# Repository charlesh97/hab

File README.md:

# HAB — High Altitude Balloon Project

## Overview

This project builds a high‑altitude balloon payload and matching ground station capable of:
- Capturing and transmitting onboard sensor data and imagery from the stratosphere
- Streaming a high‑bandwidth video downlink using DVB‑S2
- Sending a robust QPSK packet telemetry link for flight state (GPS, altitude, environment)

## Quick Start

Want to run the composite link yourself? See **[docs/RF_LINK_RUNBOOK.md](docs/RF_LINK_RUNBOOK.md)** —
hardware, validated config, full TX/RX parameter breakdown, video bridge,
soak harness, and known gotchas.

## System Architecture

### Balloon Payload
- Embedded Linux board (Rock 2A / Orange Pi Zero 3)
- HackRF SDR as RF front end for transmission
- Cameras for video capture
- Weather and atmospheric sensors (see Sensor Suite)

### RF Links (two downlinks)
1. Video downlink: DVB‑S2
2. Telemetry downlink: QPSK packet telemetry (GPS, barometric altitude, temperature, etc.)

### Ground Station
- HackRF SDR receiver
- Custom GUI in `gui/` to:
  - Demodulate DVB‑S2 video
  - Demodulate QPSK telemetry packets
  - Provide real‑time spectrum analysis and monitoring
  - Display and log telemetry

## Repository Structure (empty, still building out)
```
hab/
├── gui/          # Ground station GUI (PySide6 + GNU Radio + SoapySDR)
├── firmware/        # ESP32 + Zephyr RTOS firmware (sensors/control as needed)
├── rf/          # RF link utilities, GNU Radio graphs, tools
├── mechanical/       # Mechanical designs and enclosure files
├── photos/           # Project photos and documentation images
└── README.md         # This file
```

Refer to `gui/README.md` for detailed ground‑station setup (GNU Radio, SoapySDR, HackRF) and run instructions.

## Current Status
- ✅ Ground station GUI scaffolding complete; HackRF integration in place
- 🚧 Bringing up GUI ground station to receive DVB‑S2 video and QPSK telemetry
- 📋 Next: Full telemetry pipeline and end‑to‑end flight test

## Sensor Suite (examples)

### Core sensors (essential)
- BME280/BME680 — Temperature, pressure, humidity (I2C)
- GPS module (u‑blox NEO‑M8N/M9N class) — Lat/Lon/Altitude, velocity (UART)

### Extended sensors (recommended)
- VEML6075 — UVA/UVB index (I2C)
- MQ131 (or electrochemical O3 sensor) — Ozone concentration (analog)
- PMS5003 — Particulate matter PM2.5/PM10 (UART)
- Geiger counter module — Cosmic radiation (pulse count)
- MAG3110 (or HMC5883L) — Magnetometer (I2C)
- MPU6050 (or ICM‑20948) — IMU 6‑9 DOF (I2C/SPI)

## Getting Started (Ground Station)
1. See `gui/README.md` for system dependencies (Homebrew installs), venv setup, and running the app
2. Connect HackRF, configure frequency/sample rate/gains in the Connection tab
3. Start reception in the Telemetry tab; verify spectrum and packet flow

## References
- Orange Pi Zero 3 documentation (see PDFs in repo root)
- GNU Radio project and DVB‑S2 resources
- HackRF documentation (Great Scott Gadgets)

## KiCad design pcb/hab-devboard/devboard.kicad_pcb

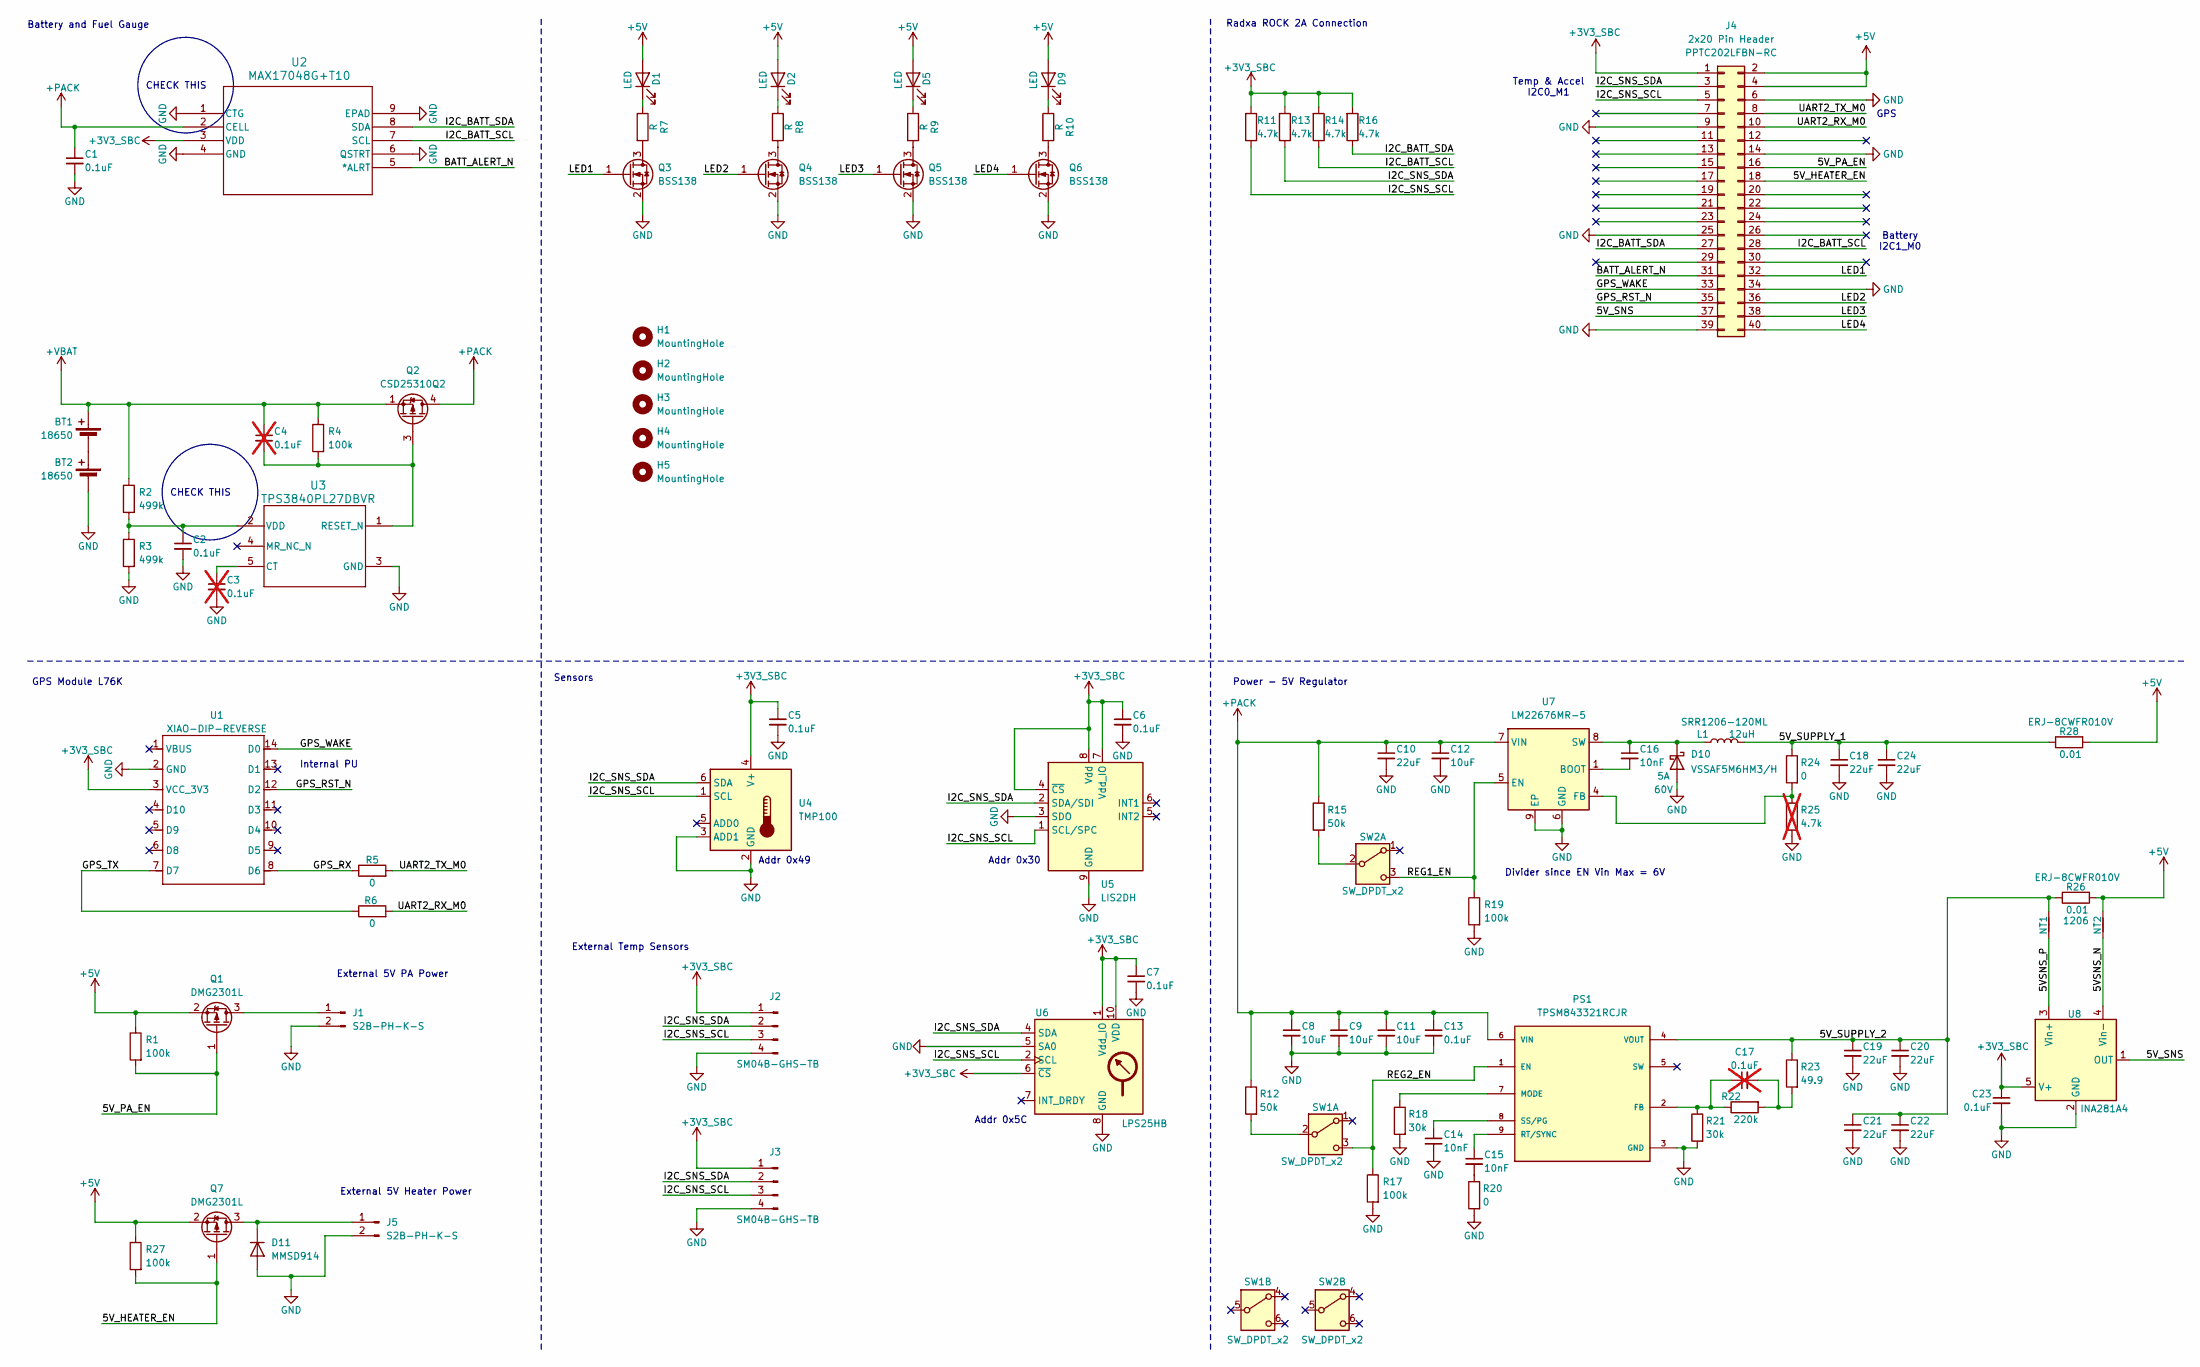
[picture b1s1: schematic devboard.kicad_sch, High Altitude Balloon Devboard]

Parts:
BT1, BT2: 18650; KEYSTONE_54_18650
C1, C2, C5, C6, C7, C13, C23: 0.1uF; C_0402_1005Metric
C3, C4, C17: 0.1uF; C_0402_1005Metric; not fitted
C8, C9, C11, C12: 10uF; C_0805_2012Metric
C10, C18, C19, C20, C21, C22, C24: 22uF; C_1206_3216Metric
C14, C15, C16: 10nF; C_0402_1005Metric
D1, D2, D5, D9: LED; LED_0805_2012Metric
D10: VSSAF5M6HM3/H; VISHAY_DO_221AC; Voltage 60V
D11: MMSD914; D_SOD-123
H1, H2, H3, H4, H5: MountingHole; MountingHole_3.2mm_M3
J1, J5: S2B-PH-K-S; JST_PH_S2B-PH-K_1x02_P2.00mm_Horizontal
J2, J3: SM04B-GHS-TB; JST_GH_SM04B-GHS-TB_1x04-1MP_P1.25mm_Horizontal
J4: 2x20 Pin Header; PinSocket_2x20_P2.54mm_Vertical; Part Number PPTC202LFBN-RC
L1: 12uH; IND_BOURNS_SRR1206; Part Number SRR1206-120ML
NT1, NT2: NetTie_2; NetTie-2_SMD_Pad0.5mm
PS1: TPSM843321RCJR; MODULE_TPSM843321RCJR; PARTREV March 2025
Q1, Q7: DMG2301L; SOT-23
Q2: CSD25310Q2; Texas_DQK
Q3, Q4, Q5, Q6: BSS138; SOT-23
R1, R4, R17, R19, R27: 100k; R_0603_1608Metric
R2, R3: 499k; R_0603_1608Metric
R5, R6, R20, R24: 0; R_0603_1608Metric
R7, R8, R9, R10: R; R_0603_1608Metric
R11, R13, R14, R16: 4.7k; R_0603_1608Metric
R12, R15: 50k; R_0603_1608Metric
R18, R21: 30k; R_0603_1608Metric
R22: 220k; R_0603_1608Metric
R23: 49.9; R_0603_1608Metric
R25: 4.7k; R_0603_1608Metric; not fitted
R26, R28: 0.01; R_1206_3216Metric; Part Number ERJ-8CWFR010V
SW1, SW2: SW_DPDT_x2; SW_DPDT_CK_JS202011JCQN
U1: XIAO-DIP-REVERSE; XIAO-DIP-SMT
U2: MAX17048G+T10; MAX17048_DFN
U3: TPS3840PL27DBVR; SOT-23-5
U4: TMP100; SOT-23-6
U5: LIS2DH; LGA-14_2x2mm_P0.35mm_LayoutBorder3x4y
U6: LPS25HB; ST_HLGA-10_2.5x2.5mm_P0.6mm_LayoutBorder3x2y
U7: LM22676MR-5; TI_SO-PowerPAD-8
U8: INA281A4; SOT-23-5

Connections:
+3V3_SBC: C5.1, C6.1, C7.1, C23.1, J2.1, J3.1, J4.1, R11.2, R13.2, R14.2, R16.2, U1.3 (VCC_3V3), U2.3 (VDD), U4.4 (V+), U5.4 (~CS), U5.7 (Vdd_IO), U5.8 (Vdd), U6.1 (Vdd_IO), U6.6 (~CS), U6.10 (VDD), U8.5 (V+)
+5V: D1.2 (A), D2.2 (A), D5.2 (A), D9.2 (A), J4.2, J4.4, NT2.2, Q1.2 (S), Q7.2 (S), R1.1, R26.2, R27.1, R28.2
+PACK: C1.1, C8.1, C9.1, C10.1, C11.1, C12.1, C13.1, PS1.6 (VIN), Q2.4 (D), Q2.7 (D), R12.1, R15.1, U2.2 (CELL), U7.7 (VIN)
+VBAT: BT1.1 (+), C4.1, Q2.1 (S), Q2.2 (S), Q2.5 (S), Q2.6 (S), Q2.8 (S), R2.1, R4.1
/5VSNS_N: NT2.1, U8.4 (Vin-)
/5VSNS_P: NT1.1, U8.3 (Vin+)
/5V_HEATER_EN: J4.18, Q7.1 (G), R27.2
/5V_PA_EN: J4.16, Q1.1 (G), R1.2
/5V_SNS: J4.37, U8.1 (OUT)
/5V_SUPPLY_1: C18.1, C24.1, L1.2, R24.1, R28.1
/5V_SUPPLY_2: C19.1, C20.1, C21.1, C22.1, NT1.2, PS1.4 (VOUT), R23.1, R26.1
/BATT_ALERT_N: J4.31, U2.5 (*ALRT)
/GPS_RST_N: J4.35, U1.12 (D2)
/GPS_RX: R5.1, U1.8 (D6)
/GPS_TX: R6.1, U1.7 (D7)
/GPS_WAKE: J4.33, U1.14 (D0)
/I2C_BATT_SCL: J4.28, R14.1, U2.7 (SCL)
/I2C_BATT_SDA: J4.27, R16.1, U2.8 (SDA)
/I2C_SNS_SCL: J2.3, J3.3, J4.5, R11.1, U4.1 (SCL), U5.1 (SCL/SPC), U6.2 (SCL)
/I2C_SNS_SDA: J2.2, J3.2, J4.3, R13.1, U4.6 (SDA), U5.2 (SDA/SDI), U6.4 (SDA)
/LED1: J4.32, Q3.1 (G)
/LED2: J4.36, Q4.1 (G)
/LED3: J4.38, Q5.1 (G)
/LED4: J4.40, Q6.1 (G)
/REG1_EN: R19.1, SW2.3 (C), U7.5 (EN)
/REG2_EN: PS1.1 (EN), R17.1, SW1.3 (C)
/UART2_RX_M0: J4.10, R6.2
/UART2_TX_M0: J4.8, R5.2
GND: BT2.2 (-), C1.2, C2.2, C3.2, C5.2, C6.2, C7.2, C8.2, C9.2, C10.2, C11.2, C12.2, C13.2, C14.2, C18.2, C19.2, C20.2, C21.2, C22.2, C23.2, C24.2, D10.2 (A), D11.2 (A), J1.2, J2.4, J3.4, J4.6, J4.9, J4.14, J4.25, J4.34, J4.39, J5.2, PS1.3 (GND), Q3.2 (S), Q4.2 (S), Q5.2 (S), Q6.2 (S), R3.2, R17.2, R18.2, R19.2, R20.2, R21.2, R25.2, U1.2 (GND), U2.1 (CTG), U2.4 (GND), U2.6 (QSTRT), U2.9 (EPAD), U3.3 (GND), U4.2 (GND), U4.3 (ADD1), U5.3 (SDO), U5.9 (GND), U5.10 (GND), U5.11 (GND), U5.12 (GND), U5.13 (GND), U5.14 (GND), U6.3 (GND), U6.5 (SA0), U6.8 (GND), U6.9 (GND), U7.6 (GND), U7.9 (EP), U8.2 (GND)
unnamed: BT1.2 (-), BT2.1 (+)
unnamed: C15.2, R20.1
unnamed: C17.2, R22.2, R23.2
unnamed: D1.1 (K), R7.1
unnamed: D2.1 (K), R8.1
unnamed: D5.1 (K), R9.1
unnamed: D9.1 (K), R10.1
unnamed: C16.1, D10.1 (K), L1.1, U7.8 (SW)
unnamed: D11.1 (K), J5.1, Q7.3 (D)
unnamed: J1.1, Q1.3 (D)
unnamed: C17.1, PS1.2 (FB), R21.1, R22.1
unnamed: PS1.7 (MODE), R18.1
unnamed: C15.1, PS1.9 (RT/SYNC)
unnamed: C14.1, PS1.8 (SS/PG)
unnamed: C4.2, Q2.3 (G), R4.2, U3.1 (RESET_N)
unnamed: Q3.3 (D), R7.2
unnamed: Q4.3 (D), R8.2
unnamed: Q5.3 (D), R9.2
unnamed: Q6.3 (D), R10.2
unnamed: R12.2, SW1.2 (B)
unnamed: R15.2, SW2.2 (B)
unnamed: C3.1, U3.5 (CT)
unnamed: C2.1, R2.2, R3.1, U3.2 (VDD)
unnamed: C16.2, U7.1 (BOOT)
unnamed: R24.2, R25.1, U7.4 (FB)

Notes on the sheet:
Temp & Accel I2C0_M1
Addr 0x49
Power - 5V Regulator
CHECK THIS
External 5V Heater Power
GPS
Battery and Fuel Gauge
Addr 0x5C
Addr 0x30
External 5V PA Power
External Temp Sensors
GPS Module L76K
Radxa ROCK 2A Connection
Battery I2C1_M0
Sensors
Divider since EN Vin Max = 6V
Internal PU

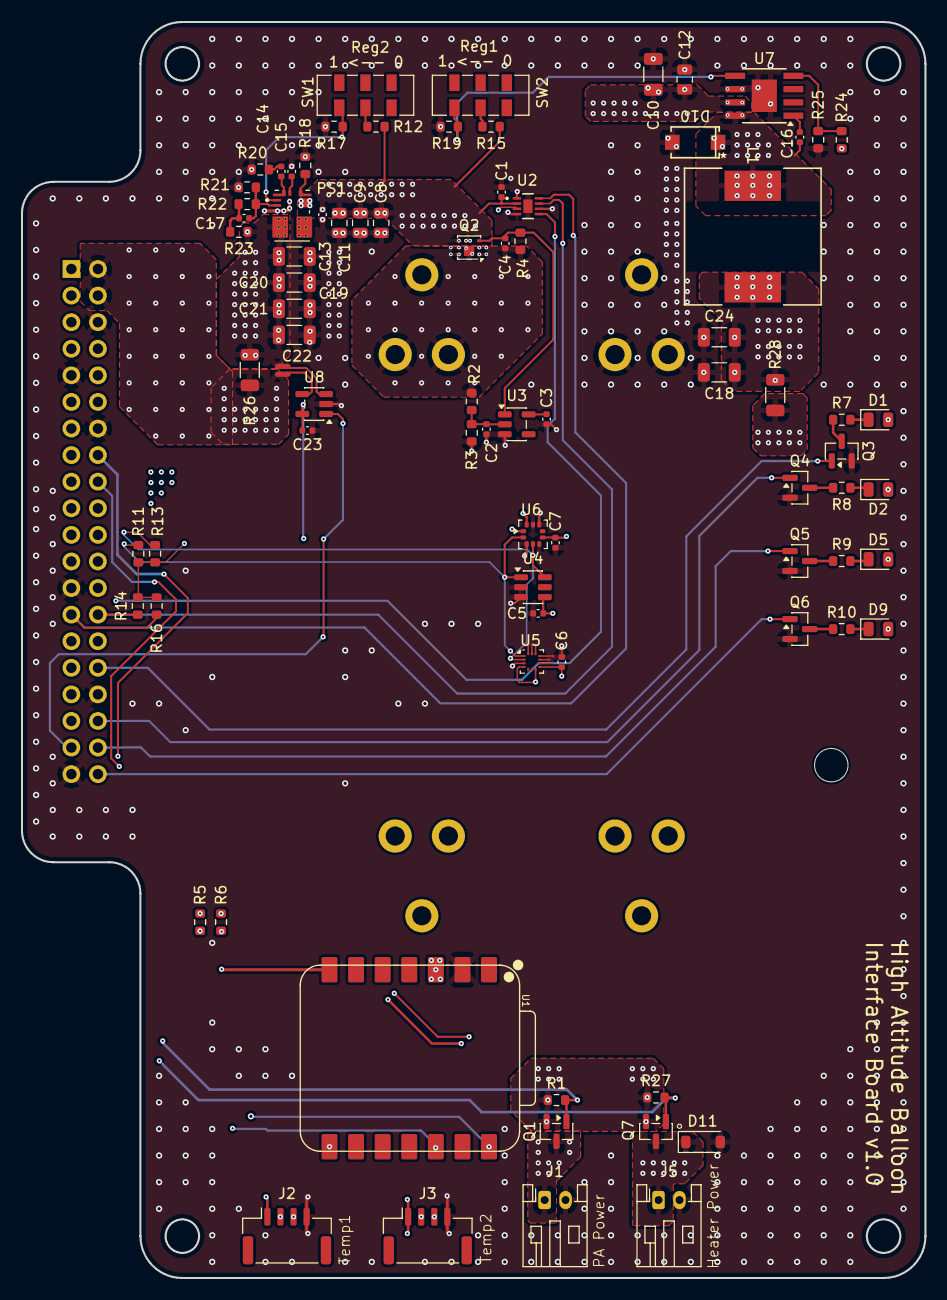
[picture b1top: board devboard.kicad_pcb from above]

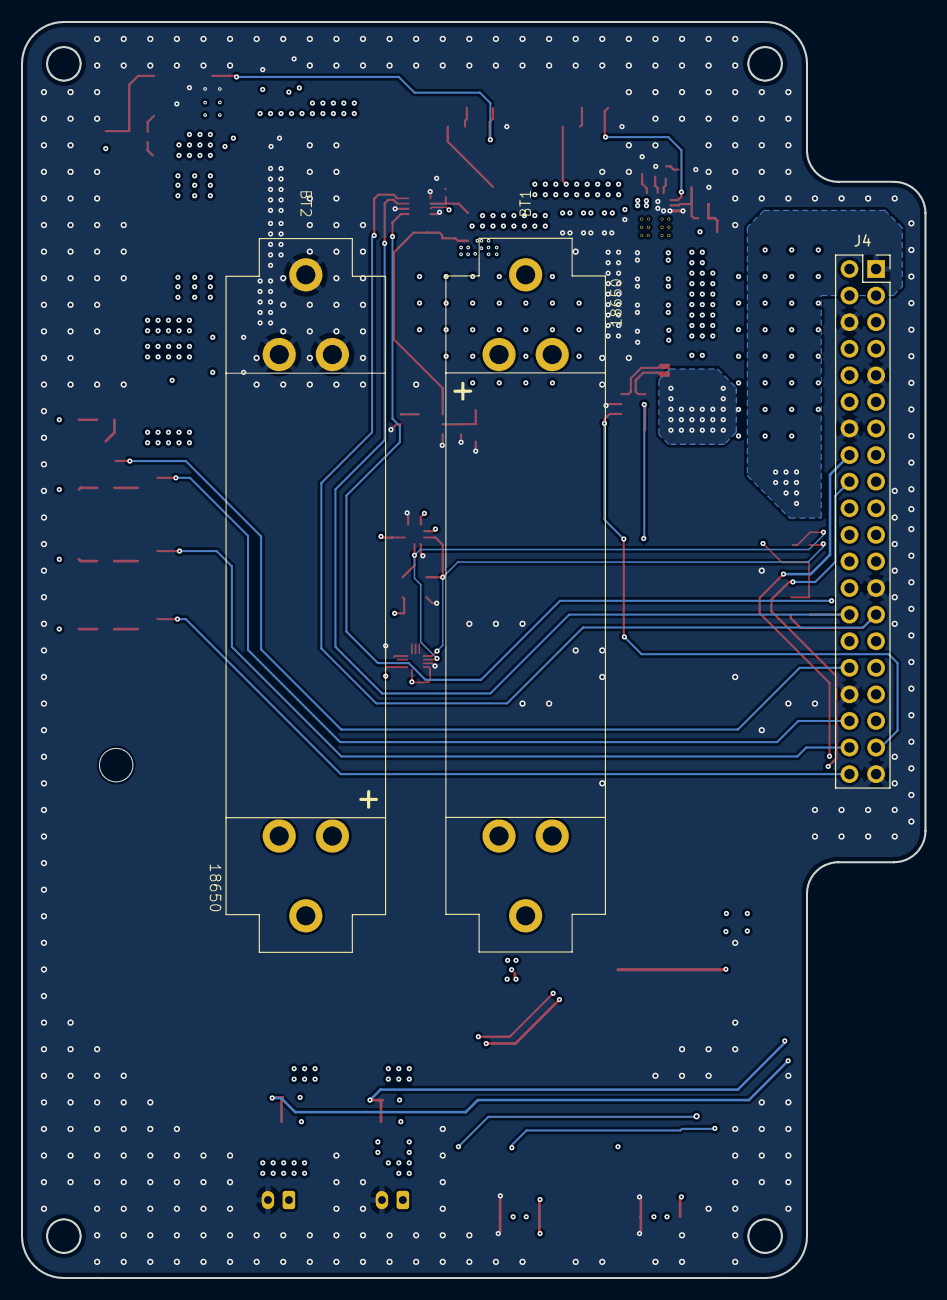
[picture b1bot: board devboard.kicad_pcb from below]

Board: 4 copper layers, 86.3 x 120.0 mm, 91 parts (3 on the bottom side), 54 nets.

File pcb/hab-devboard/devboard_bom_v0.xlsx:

devboard
Reference | Qty | Value | DNP | Exclude from BOM | Exclude from Board | Footprint | Datasheet | Part Number
BT1,BT2 | 2 | 18650 |  |  |  | hab_library:KEYSTONE_54_18650 | ~
C1,C2,C5,C6,C7,C13,C23 | 7 | 0.1uF |  |  |  | Capacitor_SMD:C_0402_1005Metric | ~
C3,C4,C17 | 3 | 0.1uF | DNP |  |  | Capacitor_SMD:C_0402_1005Metric | ~
C8,C9,C11,C12 | 4 | 10uF |  |  |  | Capacitor_SMD:C_0805_2012Metric | ~
C10,C18,C19,C20,C21,C22,C24 | 7 | 22uF |  |  |  | Capacitor_SMD:C_1206_3216Metric | ~
C14,C15,C16 | 3 | 10nF |  |  |  | Capacitor_SMD:C_0402_1005Metric | ~
D1,D2,D5,D9 | 4 | LED |  |  |  | LED_SMD:LED_0805_2012Metric | ~
D10 | 1 | VSSAF5M6HM3/H |  |  |  | hab_library:VISHAY_DO_221AC | ~
D11 | 1 | MMSD914 |  |  |  | Diode_SMD:D_SOD-123 | https://www.onsemi.com/pub/Collateral/MMSD914T1-D.PDF
H1,H2,H3,H4,H5 | 5 | MountingHole |  | Excluded from BOM |  | MountingHole:MountingHole_3.2mm_M3 | ~
J1,J5 | 2 | S2B-PH-K-S |  |  |  | Connector_JST:JST_PH_S2B-PH-K_1x02_P2.00mm_Horizontal | ~
J2,J3 | 2 | SM04B-GHS-TB |  |  |  | Connector_JST:JST_GH_SM04B-GHS-TB_1x04-1MP_P1.25mm_Horizontal | ~
J4 | 1 | 2x20 Pin Header |  |  |  | Connector_PinSocket_2.54mm:PinSocket_2x20_P2.54mm_Vertical | ~ | PPTC202LFBN-RC
L1 | 1 | 12uH |  |  |  | hab_library:IND_BOURNS_SRR1206 | ~ | SRR1206-120ML
NT1,NT2 | 2 | NetTie_2 |  | Excluded from BOM |  | NetTie:NetTie-2_SMD_Pad0.5mm | ~
PS1 | 1 | TPSM843321RCJR |  |  |  | hab_library:MODULE_TPSM843321RCJR
Q1,Q7 | 2 | DMG2301L |  |  |  | Package_TO_SOT_SMD:SOT-23 | https://www.diodes.com/assets/Datasheets/DMG2301L.pdf
Q2 | 1 | CSD25310Q2 |  |  |  | Package_SON:Texas_DQK | https://www.ti.com/lit/ds/slps234b/slps234b.pdf
Q3,Q4,Q5,Q6 | 4 | BSS138 |  |  |  | Package_TO_SOT_SMD:SOT-23 | https://www.onsemi.com/pub/Collateral/BSS138-D.PDF
R1,R4,R17,R19,R27 | 5 | 100k |  |  |  | Resistor_SMD:R_0603_1608Metric | ~
R2,R3 | 2 | 499k |  |  |  | Resistor_SMD:R_0603_1608Metric | ~
R5,R6,R20,R24 | 4 | 0 |  |  |  | Resistor_SMD:R_0603_1608Metric | ~
R7,R8,R9,R10 | 4 | R |  |  |  | Resistor_SMD:R_0603_1608Metric | ~
R11,R13,R14,R16 | 4 | 4.7k |  |  |  | Resistor_SMD:R_0603_1608Metric | ~
R12,R15 | 2 | 50k |  |  |  | Resistor_SMD:R_0603_1608Metric | ~
R18,R21 | 2 | 30k |  |  |  | Resistor_SMD:R_0603_1608Metric | ~
R22 | 1 | 220k |  |  |  | Resistor_SMD:R_0603_1608Metric | ~
R23 | 1 | 49.9 |  |  |  | Resistor_SMD:R_0603_1608Metric | ~
R25 | 1 | 4.7k | DNP |  |  | Resistor_SMD:R_0603_1608Metric | ~
R26,R28 | 2 | 0.01 |  |  |  | Resistor_SMD:R_1206_3216Metric | ~ | ERJ-8CWFR010V
SW1,SW2 | 2 | SW_DPDT_x2 |  |  |  | Button_Switch_SMD:SW_DPDT_CK_JS202011JCQN | ~
U1 | 1 | XIAO-DIP-REVERSE |  |  |  | hab_library:XIAO-DIP-SMT
U2 | 1 | MAX17049G+T10 |  |  |  | hab_library:MAX17048_DFN | MAX17048G+T10
U3 | 1 | TPS3840PL27DBVR |  |  |  | Package_TO_SOT_SMD:SOT-23-5 | https://www.ti.com/lit/gpn/tps3840-q1
U4 | 1 | TMP100 |  |  |  | Package_TO_SOT_SMD:SOT-23-6 | http://www.ti.com/lit/gpn/tmp100
U5 | 1 | LIS2DH |  |  |  | Package_LGA:LGA-14_2x2mm_P0.35mm_LayoutBorder3x4y | http://www.st.com/web/en/resource/technical/document/datashe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
U6 | 1 | LPS25HB |  |  |  | Package_LGA:ST_HLGA-10_2.5x2.5mm_P0.6mm_LayoutBorder3x2y | https://www.st.com/resource/en/datasheet/lps25hb.pdf
U7 | 1 | LM22676MR-5 |  |  |  | Package_SO:TI_SO-PowerPAD-8 | http://www.ti.com/lit/ds/symlink/lm22676.pdf
U8 | 1 | INA281A4 |  |  |  | Package_TO_SOT_SMD:SOT-23-5 | https://www.ti.com/lit/ds/symlink/ina281.pdf

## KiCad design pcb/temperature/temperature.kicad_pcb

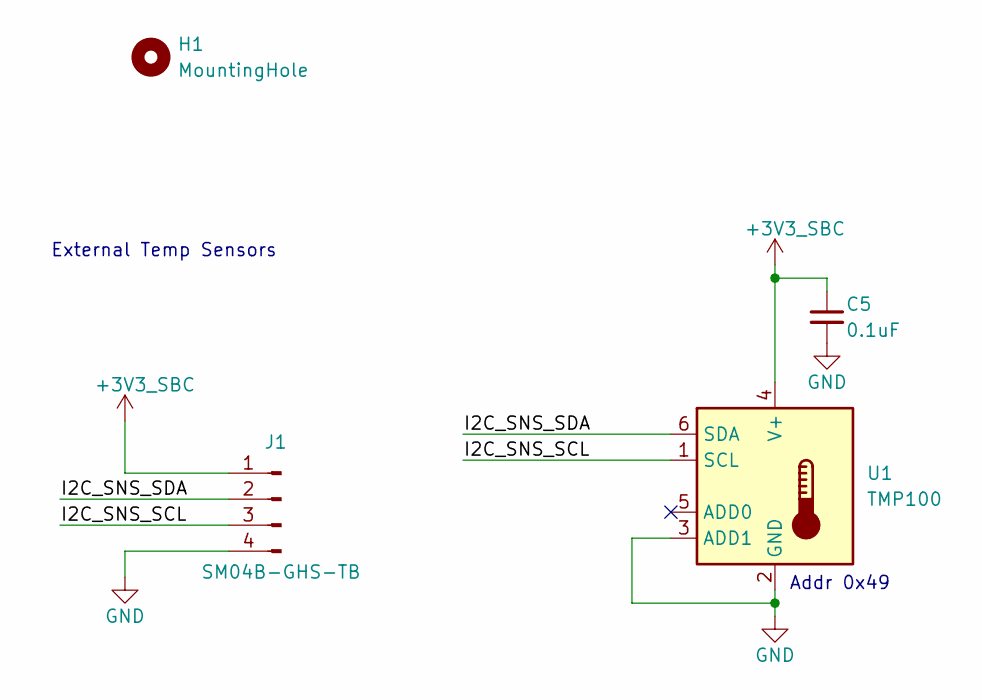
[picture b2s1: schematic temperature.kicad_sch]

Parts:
C5: 0.1uF; C_0402_1005Metric
H1: MountingHole; MountingHole_3.2mm_M3
J1: SM04B-GHS-TB; JST_GH_SM04B-GHS-TB_1x04-1MP_P1.25mm_Horizontal
U1: TMP100; SOT-23-6

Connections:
+3V3_SBC: C5.1, J1.1, U1.4 (V+)
/I2C_SNS_SCL: J1.3, U1.1 (SCL)
/I2C_SNS_SDA: J1.2, U1.6 (SDA)
GND: C5.2, J1.4, U1.2 (GND), U1.3 (ADD1)

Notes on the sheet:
Addr 0x49
External Temp Sensors

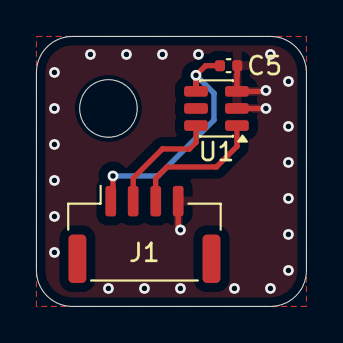
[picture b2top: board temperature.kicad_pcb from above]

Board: 2 copper layers, 15.0 x 15.0 mm, 4 parts (0 on the bottom side), 4 nets.

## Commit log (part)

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2025-08-10 Add hab-esp32 hab-gui couple of files, in preparation for developing a wireless telemetry link for balloon
2025-10-27 Added dtv-utils to calculate the required bitrate for video transmission, updated dvbs2_tx.py, added new vibecoded files for hab gui still WIP
2025-10-28 Add README
2025-10-28 Revise repository structure section in README
    Updated the repository structure section to indicate it is still under construction.
2025-11-16 pcb updates, created temperature board, finished devboard
2025-11-24 Updating pcb, adding xcode project for macOS gui
2025-11-29 updated pcb bom, rebuild some esp32 files
2025-11-29 Minor changes
2025-12-01 Worked through issue with packet transmission from gnuradio packet-loopback example, see rf-link/packet
2025-12-01 tried to add padding for tx burst packets
2025-12-13 Found a bug in the padding_packing block workaround that was only testing the CRC on a fixed appended 2bits on the output of the fec decoder (implicitly drops 2bits due to the CC selection defaulted 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
2026-05-11 feat(rf-link): BPSK packet link — HELLO WORLD TX/RX proven at 5,800+ packets/20s
    Add native Python BPSK packet transmitter and receiver that successfully
    sent and decoded 'HELLO WORLD\n' over an SMA cable between two HackRF Ones.
    Key findings during development:
    - Sync-word correlation (0xE38FC0FC) beats preamble correlation for exact
    packet boundaries — the 256-bit alternating preamble gives flat peaks
    - GNU Radio map_bb([1,-1]) wraps -1 to 255, killing BPSK. Fixed with direct
2026-05-11 feat(rf-link): enhanced TX/RX with CRC+FEC packet protection
    New packet structure (aligned to original packet_rx.py):
    [preamble: 24 bytes (192 bits)] [sync: 32-bit access code]
    [FEC payload: variable length, CRC-32 protected]
    Preamble: 0xE38FC0FC7FC7E381C0FF8038FFF038E00FC0038000FFFFC0
    (from packet_rx.py preamble_rep)
    Sync word: 0xACDDA4E2 (GNU Radio default access code, NOT in preamble
2026-05-11 docs(rf-link): update documentation with enhanced chain
    HELLO_TX_RX.md now describes both the legacy and enhanced packet
    structures. ALIGNMENT_PLAN.md tracks progress on all 6 alignment steps.
2026-05-11 fix(rf-link): increase max_payload to 512 with 2-byte length field
    1 byte length only supports 0-255. Bumped to 2 bytes (big-endian) for
    512 max payload, with room up to 65535.
    Also fixed process_phase to extract variable-length FEC payloads:
    - No longer requires full MAX_FEC_SYMS to exist after sync word
    - Extracts min(available, MAX_FEC_SYMS) and lets packet_decode()
    handle undersized input via embedded length byte + CRC
2026-05-11 test(rf-link): formal 3-layer test suite
    Layer 1 — Direct Codec Unit Tests (ms): encode/decode round-trip for
    11 payload sizes, empty, binary, oversized, max_payload rejection,
    corruption detection, size predictions.
    Layer 2 — RF Software Loopback (seconds): full TX→RX pipeline in
    software — BPSK modulate, IQ save/load, FO scan, RRC filter,
    decimate, sync correlate, FEC decode, CRC validate. Tests single
2026-05-13 Fix FO estimation for hardware: correlation-based scan_frequency replaces biased centroid
    - scan_frequency() now uses sync-word correlation to find FO (±20kHz sweep, 500Hz step)
    - Falls back to spectral centroid for software loopback (FO ≈ 0)
    - Fixes test_layer3.py: assigns distinct serial numbers to TX/RX HackRFs
    instead of both opening 'driver=hackrf' (device conflict)
    - Hardware proven: FO=-6500/7200Hz decodes 'HELLO HARDWARE' from captured IQ
    Offline decode verified. Layers 1+2 pass all tests. SoapySDR/GNU Radio TX
2026-05-13 Fix code review findings: SYNC_BPSK polarity, docstrings, dead code, import scope
    - Fix SYNC_BPSK polarity in pkt_enhanced_rx.py: now matches TX mapping
    (bit 0->+1, bit 1->-1) using -2.0*bit+1.0 instead of 2.0*bit-1.0
    - Fix docstring defaults in packet_codec.py: max_payload default 512
    (not 256), +2 length bytes (not +1)
    - Remove dead _bits_to_bytes() helper in packet_codec.py
    - Move gnuradio imports to local scope in pkt_enhanced_tx.py so
2026-05-17 step3: variable SPS, burst shaping, AGC, FO tracking + bug fixes
2026-05-17 Update Layer 3 for Step 3: variable SPS, AGC, FO tracking support
2026-05-17 Fix hardware decode: sync-word FO refinement + energy threshold + Layer 3 subprocess
    Root cause: Three issues prevented hardware cable loopback from decoding.
    1. AGC applied before FO estimation destroyed energy detection:
    - scan_frequency finds energy peaks, but AGC normalizes noise floor
    to the same RMS as signal, making detection impossible
    - Fix: Estimate FO on RAW samples (DC-blocked, no AGC)
    2. Energy detection threshold hardcoded at 10, but HackRF via SoapySDR
2026-05-17 Step 3 final: scan_frequency 4-phase fix + Codex review findings
    - scan_frequency: reduced from 20 to 4 phases (was 10x slower than
    original 2-phase version — caused ~25s per chunk, only 1 chunk
    processed per 30s run)
    - Fixed file-mode bb.real → bb (Codex finding: dropping Q channel
    would fail for recorded signals with real FO)
    - Cleaned up debug test scripts (test_hw_*.py)
2026-05-18 HAB Ground Station v0.1 — Full pipeline buildout
    ## Python Backend
    - Fixed dvbs2_flowgraph.py: corrected soapy_hackrf_sink_0 bug, set_freq→set_frequency, added real FFT spectrum extraction
    - Built HabEngine (singleton orchestrator): FlowgraphManager, PipelineManager, WebSocket server
    - Refactored GUI tabs (Connection, DVBS2-TX, Telemetry) to use HabEngine
    - Added Dashboard tab with live metric cards (engine, device, pipeline, TX, frequency, bitrate)
    - Created hab_engine/ package with typed data models (SpectrumFrame, PipelineStatus, EngineStatus, DeviceInfo)
2026-05-18 HAB Ground Station v0.2 — Cinematic visual refactor + WebSocket live test
    ## Visual Redesign
    - Completed rewritten QT stylesheet: #0a0a0b dark theme, glassmorphism cards, pill navigation
    - New hab_engine/widgets.py: GlassCard, MetricTile, StatusPill, NavPill, PrimaryButton, TopBar, Divider
    - Dashboard tab: MetricTile grid with status-colored values, system info panel
    - Connection tab: GlassCard sections for device discovery, RF params, log
    - DVBS2-TX tab: Split pipeline/TX controls, spectrum waterfall with orange accent
2026-05-18 HAB Ground Station v0.3.1 — Full-web MVP feature complete
    ## Dashboard Pages
    - Overview: HeroStage (telemetry card) + Spectrum mini-widget + bottom modules (AssetCard, MissionSettingsGrid, TrajectoryCard) + StatusBar
    - Telemetry: SpectrumWaterfall (real-time FFT canvas) + TelemetryGrid (9 stat tiles) + TelemetryCharts (altitude + temp) + LowerTabs (Video Feeds / RF Config / Data Stream)
    - Map: Full-screen FlightMap (Leaflet) with balloon position, flight path, predicted trajectory overlay
    - Settings: Dark-themed RF Config panel with functional controls (freq, VGA, AMP, symbol rate) wired to API
    ## Backend API (server.py)
2026-05-18 HAB Ground Station v0.4 — Multi-page dark dashboard with live data
    ## New Features (this session)
    - SSE spectrum streaming (EventSource, 10Hz, fallback to HTTP polling)
    - Real-time spectrum waterfall (canvas-based, 5-stop color gradient)
    - Device Status Panel (4-column: HackRF, Pipeline, TX, WebSocket)
    - Live telemetry packet generator (1-3s intervals, TLM/EVT/WARN)
    - Animated connection indicator (pulse when data flowing)
2026-05-20 Add mission control dashboard design specs and Gemini wireframe prompts
2026-05-20 Add mission control dashboard implementation plan
2026-05-20 feat: update Tailwind theme, types, and styles for mission control dashboard
2026-05-20 feat: add Sidebar component and replace TopBar for mission control dashboard
2026-05-20 feat: add CameraFeed, PacketStream, and MissionControl components (Tasks 6+7)
2026-05-20 feat: integrate mission control app shell with new two-view architecture
2026-05-20 feat: build settings page with 5 sub-tabs (device, RF, DVB-S2, pipeline, about)
2026-05-20 feat: finalize mission control dashboard — integration testing and production build
2026-05-20 feat: add receiver-server project skeleton
2026-05-20 feat: add Pydantic models for telemetry packets, status, and WS messages
2026-05-20 feat: add WebSocketManager with broadcast and connection tracking
2026-05-20 feat: add ReceiverManager state machine with lifecycle and error recovery
2026-05-20 feat: add ReceiverWorker (sync SDR) and AsyncPacketReceiver (async bridge)
2026-05-20 feat: add REST routes (/health, /api/packets, /api/devices) and WebSocket route with command dispatch
2026-05-20 feat: add main.py FastAPI app wiring and integration tests
2026-05-20 chore: final verification — launch.sh python3 fix and cleanup
2026-05-20 fix: use SoapySDR Python API for /api/devices (not hackrf_info CLI); broadcast status on RUNNING transition
2026-05-20 refactor: single-server architecture — receiver-server serves dashboard + simulation mode
    - receiver-server/main.py now serves dashboard static files + SPA catch-all
    - receiver_manager.py: added simulation mode (HAB_SIMULATE=1) with fake telemetry,
    spectrum generation, and periodic status broadcast loop
    - launch.sh: supports --simulate flag, shows endpoint URLs on boot
    - ws_manager.py: broadcast_status accepts both ReceiverStatus and dict
    - models.py: added WsTelemetryMessage + WsEngineStatusMessage types
2026-05-20 fix: address code review findings — remove dead WS models, fix spectrum format consistency, clean up unused fields
    - Removed all unused WS envelope Pydantic models (WsPacketMessage, WsStatusMessage,
    WsSpectrumMessage, WsErrorMessage, WsTelemetryMessage, WsEngineStatusMessage,
    CmdStart, CmdStop, CmdConfigure) from models.py — actual WS messages are
    constructed as raw dicts
    - Removed unused ServerConfig instantiation from main.py
    - Simulation spectrum loop now uses ws_manager.broadcast_spectrum() directly,
2026-06-06 feat: external packet ingestion API + standalone balloon-sim.py
    - POST /api/packet endpoint validates and ingests telemetry packets
    - ReceiverManager.ingest_packet() broadcasts to all WebSocket clients
    - balloon-sim.py: standalone CLI simulator with realistic flight profile
    (ascent → float → descent), standard-atmosphere physics, battery drain,
    configurable speed/rate/profile, and live terminal status
    - ws_manager.py: add __future__ annotations import
2026-06-06 Reorganize repo structure + add balloon telemetry simulator
    Restructured hab/ repository for clarity:
    receiver-server/ → dashboard/server/
    web-dashboard/ → dashboard/web/
    balloon-sim/ → dashboard/sim/ (new — balloon telemetry simulator)
    rf-link/ → rf/
    hab-esp32/ → firmware/
2026-06-06 feat: add per-metric rolling window buffers to useHabApi
2026-06-06 feat: add TelemetryCard with Navigation, Environment, Power&Link, and Attitude sections
2026-06-06 feat: rewrite MissionControl with Map|Video|TelemetryCard layout, pass metricHistory
2026-06-06 refactor: remove 7 obsolete data card components
2026-06-06 fix: make MapCard fill full column height
2026-06-06 chore: verify build, lint, and manual inspection pass
2026-06-06 fix: remove duplicate type definitions and dead environment prop
2026-06-06 feat: add SQLite packet persistence to ReceiverManager
2026-06-06 feat: add GET /api/positions endpoint for map trail data
2026-06-06 feat: add loadPositions function to useHabApi hook
2026-06-06 feat: replace static SVG map with live Leaflet map showing balloon trail
